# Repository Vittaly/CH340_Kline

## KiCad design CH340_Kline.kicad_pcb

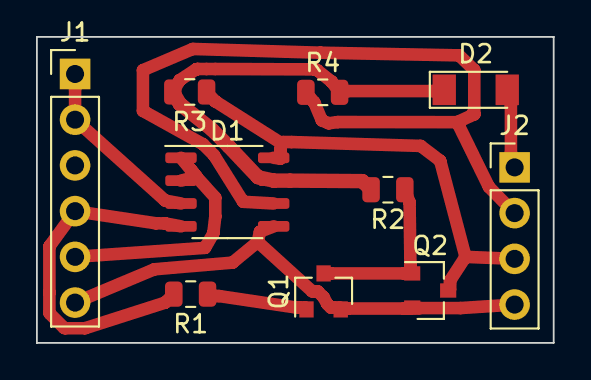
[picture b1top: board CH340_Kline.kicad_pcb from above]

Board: 2 copper layers, 28.7 x 17.0 mm, 10 parts (0 on the bottom side), 10 nets.

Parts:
D1: L9637D; SO-8_3.9x4.9mm_P1.27mm
D2: LL4148; D_MiniMELF
J1: Conn_01x06; PinHeader_1x06_P2.54mm_Vertical
J2: Conn_01x04; PinHeader_1x04_P2.54mm_Vertical
Q1, Q2: BC847; SOT-23
R1, R2: 1K; R_0805_2012Metric
R3, R4: 510R; R_0805_2012Metric

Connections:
5V: D1.3, J1.1, J1.2
GND: D1.5, J1.6, J2.4, Q1.2, Q2.2
K-line: D1.6, J2.2, R4.1
L-line: D1.8, J2.3, Q2.3, R3.1
unnamed: D2.2, J2.1
unnamed: Q1.1, R1.1
unnamed: Q1.3, Q2.1, R2.1
Rx: D1.1, D1.2, J1.5
Tx: D1.4, J1.4, R1.2
Vss: D1.7, D2.1, R2.2, R3.2, R4.2

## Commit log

2020-01-04 first
2020-01-05 routing complite
2020-01-09 add sym, add zone
